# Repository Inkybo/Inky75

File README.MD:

# Inky75 Keyboard

The Inky75 is a custom designed keyboard pcb based on the adafruit KB2040 and using the KMK firmware.

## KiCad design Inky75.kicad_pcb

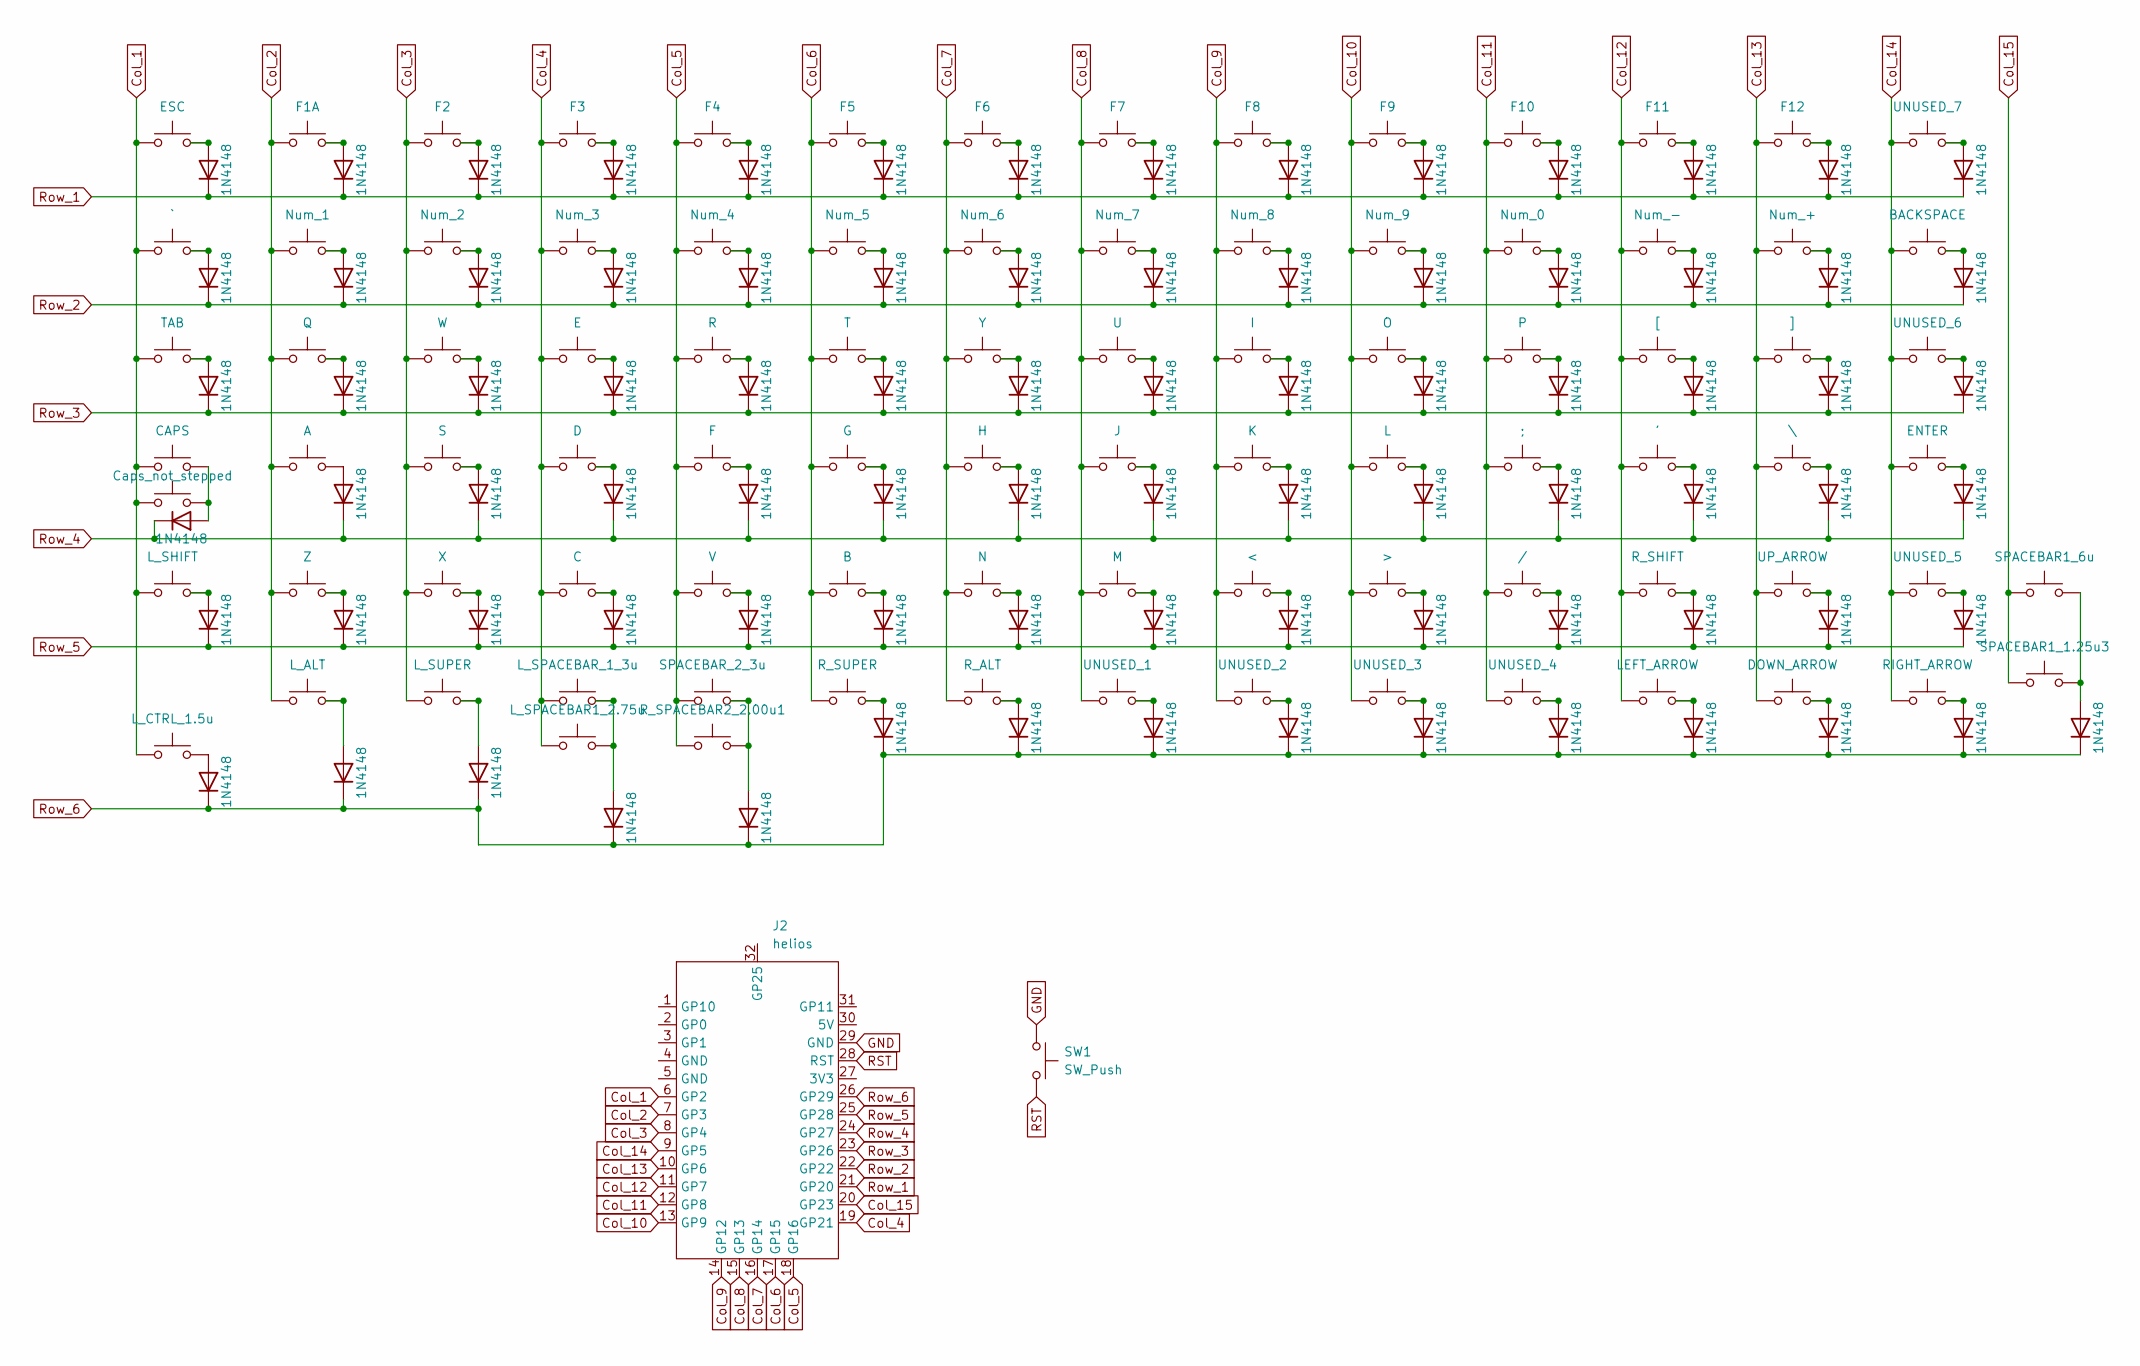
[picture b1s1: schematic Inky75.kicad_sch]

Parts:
'1: '; SW_Cherry_MX_PCB_1.00u
/1: /; SW_Cherry_MX_PCB_1.00u
;1: ;; SW_Cherry_MX_PCB_1.00u
<1: <; SW_Cherry_MX_PCB_1.00u
>1: >; SW_Cherry_MX_PCB_1.00u
A1: A; SW_Cherry_MX_PCB_1.00u
B1: B; SW_Cherry_MX_PCB_1.00u
BACKSPACE1: BACKSPACE; SW_Cherry_MX_PCB_2.00u
C1: C; SW_Cherry_MX_PCB_1.00u
Caps1: CAPS; SW_Cherry_MX_PCB_1.75u
Caps_not_stepped1: Caps_not_stepped; SW_Cherry_MX_PCB_1.25u
D1, D2, D3, D4, D5, D6, D7, D8, D9, D10, D11, D12, D13, D14, D15, D16, D17, D18, D20, D21, D22, D23, D24, D25, D26, D27, D28, D29, D30, D31, D32, D33, D34, D35, D36, D37, D38, D39, D40, D41, D42, D43, D44, D45, D46, D47, D48, D49, D50, D51, D52, D53, D54, D55, D56, D57, D58, D59, D60, D61, D62, D63, D64, D65, D66, D67, D68, D69, D70, D71, D72, D73, D74, D75, D76, D77, D78, D79, D80, D81, D82, D83, D84, D85, D86: 1N4148; D_DO-35_SOD27_P7.62mm_Horizontal
D19: D; SW_Cherry_MX_PCB_1.00u
DOWN_ARROW1: DOWN_ARROW; SW_Cherry_MX_PCB_1.00u
E1: E; SW_Cherry_MX_PCB_1.00u
ENTER1: ENTER; SW_Cherry_MX_PCB_ISOEnter
ESC1: ESC; SW_Cherry_MX_PCB_1.00u
F1: F; SW_Cherry_MX_PCB_1.00u
F1A1: F1A; SW_Cherry_MX_PCB_1.00u
F2: F2; SW_Cherry_MX_PCB_1.00u
F3: F3; SW_Cherry_MX_PCB_1.00u
F4: F4; SW_Cherry_MX_PCB_1.00u
F5: F5; SW_Cherry_MX_PCB_1.00u
F6: F6; SW_Cherry_MX_PCB_1.00u
F7: F7; SW_Cherry_MX_PCB_1.00u
F8: F8; SW_Cherry_MX_PCB_1.00u
F9: F9; SW_Cherry_MX_PCB_1.00u
F10: F10; SW_Cherry_MX_PCB_1.00u
F11: F11; SW_Cherry_MX_PCB_1.00u
F12: F12; SW_Cherry_MX_PCB_1.00u
G1: G; SW_Cherry_MX_PCB_1.00u
H1: H; SW_Cherry_MX_PCB_1.00u
I1: I; SW_Cherry_MX_PCB_1.00u
J1: J; SW_Cherry_MX_PCB_1.00u
J2: helios; helios_no-usb
K1: K; SW_Cherry_MX_PCB_1.00u
L1: L; SW_Cherry_MX_PCB_1.00u
LEFT_ARROW1: LEFT_ARROW; SW_Cherry_MX_PCB_1.00u
L_ALT1: L_ALT; SW_Cherry_MX_PCB_1.25u
L_CTRL_1.5u1: L_CTRL_1.5u; SW_Cherry_MX_PCB_1.50u
L_SHIFT1: L_SHIFT; SW_Cherry_MX_PCB_2.25u
L_SPACEBAR1: L_SPACEBAR_1_3u; SW_Cherry_MX_PCB_3.00u
L_SPACEBAR1_2.75u1: L_SPACEBAR1_2.75u; SW_Cherry_MX_PCB_2.75u
L_SUPER1: L_SUPER; SW_Cherry_MX_PCB_1.50u
M1: M; SW_Cherry_MX_PCB_1.00u
N1: N; SW_Cherry_MX_PCB_1.00u
Num_0: Num_0; SW_Cherry_MX_PCB_1.00u
Num_1: Num_1; SW_Cherry_MX_PCB_1.00u
Num_2: Num_2; SW_Cherry_MX_PCB_1.00u
Num_3: Num_3; SW_Cherry_MX_PCB_1.00u
Num_4: Num_4; SW_Cherry_MX_PCB_1.00u
Num_5: Num_5; SW_Cherry_MX_PCB_1.00u
Num_6: Num_6; SW_Cherry_MX_PCB_1.00u
Num_7: Num_7; SW_Cherry_MX_PCB_1.00u
Num_8: Num_8; SW_Cherry_MX_PCB_1.00u
Num_9: Num_9; SW_Cherry_MX_PCB_1.00u
Num_+1: Num_+; SW_Cherry_MX_PCB_1.00u
Num_-1: Num_-; SW_Cherry_MX_PCB_1.00u
O1: O; SW_Cherry_MX_PCB_1.00u
P1: P; SW_Cherry_MX_PCB_1.00u
Q1: Q; SW_Cherry_MX_PCB_1.00u
R1: R; SW_Cherry_MX_PCB_1.00u
RIGHT_ARROW1: RIGHT_ARROW; SW_Cherry_MX_PCB_1.00u
R_ALT1: R_ALT; SW_Cherry_MX_PCB_1.50u
R_SHIFT1: R_SHIFT; SW_Cherry_MX_PCB_1.75u
R_SPACEBAR2_2.00u1: R_SPACEBAR2_2.00u1; SW_Cherry_MX_PCB_2.00u
R_SUPER1: R_SUPER; SW_Cherry_MX_PCB_1.50u
S1: S; SW_Cherry_MX_PCB_1.00u
SPACEBAR1_1.25u3: SPACEBAR1_1.25u3; SW_Cherry_MX_PCB_1.25u
SPACEBAR1_6u1: SPACEBAR1_6u; SW_Cherry_MX_PCB_6.00u
SPACEBAR_2: SPACEBAR_2_3u; SW_Cherry_MX_PCB_3.00u
SW1: SW_Push; SW_SPST_TL3342
T1: T; SW_Cherry_MX_PCB_1.00u
Tab1: TAB; SW_Cherry_MX_PCB_1.50u
U2: U; SW_Cherry_MX_PCB_1.00u
UNUSED_1: UNUSED_1; SW_Cherry_MX_PCB_1.00u
UNUSED_2: UNUSED_2; SW_Cherry_MX_PCB_1.00u
UNUSED_3: UNUSED_3; SW_Cherry_MX_PCB_1.00u
UNUSED_4: UNUSED_4; SW_Cherry_MX_PCB_1.00u
UNUSED_5: UNUSED_5; SW_Cherry_MX_PCB_1.00u
UNUSED_6: UNUSED_6; SW_Cherry_MX_PCB_1.00u
UNUSED_7: UNUSED_7; SW_Cherry_MX_PCB_1.00u
UP_ARROW1: UP_ARROW; SW_Cherry_MX_PCB_1.00u
V1: V; SW_Cherry_MX_PCB_1.00u
W1: W; SW_Cherry_MX_PCB_1.00u
X1: X; SW_Cherry_MX_PCB_1.00u
Y1: Y; SW_Cherry_MX_PCB_1.00u
Z1: Z; SW_Cherry_MX_PCB_1.00u
[1: [; SW_Cherry_MX_PCB_1.00u
\1: \; SW_Cherry_MX_PCB_1.00u
]1: ]; SW_Cherry_MX_PCB_1.00u
`1: `; SW_Cherry_MX_PCB_1.00u

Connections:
Col_1: Caps1.1, Caps_not_stepped1.1, ESC1.1, J2.6 (GP2), L_CTRL_1.5u1.1, L_SHIFT1.1, Tab1.1, `1.1
Col_2: A1.1, F1A1.1, J2.7 (GP3), L_ALT1.1, Num_1.1, Q1.1, Z1.1
Col_3: F2.1, J2.8 (GP4), L_SUPER1.1, Num_2.1, S1.1, W1.1, X1.1
Col_4: C1.1, D19.1, E1.1, F3.1, J2.19 (GP21), L_SPACEBAR1.1, L_SPACEBAR1_2.75u1.1, Num_3.1
Col_5: F1.1, F4.1, J2.18 (GP16), Num_4.1, R1.1, R_SPACEBAR2_2.00u1.1, SPACEBAR_2.1, V1.1
Col_6: B1.1, F5.1, G1.1, J2.17 (GP15), Num_5.1, R_SUPER1.1, T1.1
Col_7: F6.1, H1.1, J2.16 (GP14), N1.1, Num_6.1, R_ALT1.1, Y1.1
Col_8: F7.1, J1.1, J2.15 (GP13), M1.1, Num_7.1, U2.1, UNUSED_1.1
Col_9: <1.1, F8.1, I1.1, J2.14 (GP12), K1.1, Num_8.1, UNUSED_2.1
Col_10: >1.1, F9.1, J2.13 (GP9), L1.1, Num_9.1, O1.1, UNUSED_3.1
Col_11: /1.1, ;1.1, F10.1, J2.12 (GP8), Num_0.1, P1.1, UNUSED_4.1
Col_12: '1.1, F11.1, J2.11 (GP7), LEFT_ARROW1.1, Num_-1.1, R_SHIFT1.1, [1.1
Col_13: DOWN_ARROW1.1, F12.1, J2.10 (GP6), Num_+1.1, UP_ARROW1.1, \1.1, ]1.1
Col_14: BACKSPACE1.1, ENTER1.1, J2.9 (GP5), RIGHT_ARROW1.1, UNUSED_5.1, UNUSED_6.1, UNUSED_7.1
Col_15: J2.20 (GP23), SPACEBAR1_1.25u3.1, SPACEBAR1_6u1.1
GND: J2.29 (GND), SW1.1
unnamed: '1.2, D71.2 (A)
unnamed: /1.2, D66.2 (A)
unnamed: ;1.2, D65.2 (A)
unnamed: <1.2, D54.2 (A)
unnamed: >1.2, D60.2 (A)
unnamed: A1.2, D10.2 (A)
unnamed: B1.2, D36.2 (A)
unnamed: BACKSPACE1.2, D83.2 (A)
unnamed: C1.2, D24.2 (A)
unnamed: Caps1.2, Caps_not_stepped1.2, D4.2 (A)
unnamed: D1.2 (A), ESC1.2
unnamed: D2.2 (A), `1.2
unnamed: D3.2 (A), Tab1.2
unnamed: D5.2 (A), L_SHIFT1.2
unnamed: D6.2 (A), L_CTRL_1.5u1.2
unnamed: D7.2 (A), F1A1.2
unnamed: D8.2 (A), Num_1.2
unnamed: D9.2 (A), Q1.2
unnamed: D11.2 (A), Z1.2
unnamed: D12.2 (A), L_ALT1.2
unnamed: D13.2 (A), F2.2
unnamed: D14.2 (A), Num_2.2
unnamed: D15.2 (A), W1.2
unnamed: D16.2 (A), S1.2
unnamed: D17.2 (A), X1.2
unnamed: D18.2 (A), L_SUPER1.2
unnamed: D19.2, D23.2 (A)
unnamed: D20.2 (A), F3.2
unnamed: D21.2 (A), Num_3.2
unnamed: D22.2 (A), E1.2
unnamed: D25.2 (A), L_SPACEBAR1.2, L_SPACEBAR1_2.75u1.2
unnamed: D26.2 (A), F4.2
unnamed: D27.2 (A), Num_4.2
unnamed: D28.2 (A), R1.2
unnamed: D29.2 (A), F1.2
unnamed: D30.2 (A), V1.2
unnamed: D31.2 (A), R_SPACEBAR2_2.00u1.2, SPACEBAR_2.2
unnamed: D32.2 (A), F5.2
unnamed: D33.2 (A), Num_5.2
unnamed: D34.2 (A), T1.2
unnamed: D35.2 (A), G1.2
unnamed: D37.2 (A), R_SUPER1.2
unnamed: D38.2 (A), F6.2
unnamed: D39.2 (A), Num_6.2
unnamed: D40.2 (A), Y1.2
unnamed: D41.2 (A), H1.2
unnamed: D42.2 (A), N1.2
unnamed: D43.2 (A), R_ALT1.2
unnamed: D44.2 (A), F7.2
unnamed: D45.2 (A), Num_7.2
unnamed: D46.2 (A), U2.2
unnamed: D47.2 (A), J1.2
unnamed: D48.2 (A), M1.2
unnamed: D49.2 (A), UNUSED_1.2
unnamed: D50.2 (A), F8.2
unnamed: D51.2 (A), Num_8.2
unnamed: D52.2 (A), I1.2
unnamed: D53.2 (A), K1.2
unnamed: D55.2 (A), UNUSED_2.2
unnamed: D56.2 (A), F9.2
unnamed: D57.2 (A), Num_9.2
unnamed: D58.2 (A), O1.2
unnamed: D59.2 (A), L1.2
unnamed: D61.2 (A), UNUSED_4.2
unnamed: D62.2 (A), F10.2
unnamed: D63.2 (A), Num_0.2
unnamed: D64.2 (A), P1.2
unnamed: D67.2 (A), UNUSED_3.2
unnamed: D68.2 (A), F11.2
unnamed: D69.2 (A), Num_-1.2
unnamed: D70.2 (A), [1.2
unnamed: D72.2 (A), R_SHIFT1.2
unnamed: D73.2 (A), LEFT_ARROW1.2
unnamed: D74.2 (A), F12.2
unnamed: D75.2 (A), Num_+1.2
unnamed: D76.2 (A), ]1.2
unnamed: D77.2 (A), \1.2
unnamed: D78.2 (A), UP_ARROW1.2
unnamed: D79.2 (A), DOWN_ARROW1.2
unnamed: D80.2 (A), UNUSED_7.2
unnamed: D81.2 (A), ENTER1.2
unnamed: D82.2 (A), UNUSED_6.2
unnamed: D84.2 (A), UNUSED_5.2
unnamed: D85.2 (A), RIGHT_ARROW1.2
unnamed: D86.2 (A), SPACEBAR1_1.25u3.2, SPACEBAR1_6u1.2
RST: J2.28 (RST), SW1.2
Row_1: D1.1 (K), D7.1 (K), D13.1 (K), D20.1 (K), D26.1 (K), D32.1 (K), D38.1 (K), D44.1 (K), D50.1 (K), D56.1 (K), D62.1 (K), D68.1 (K), D74.1 (K), D80.1 (K), J2.21 (GP20)
Row_2: D2.1 (K), D8.1 (K), D14.1 (K), D21.1 (K), D27.1 (K), D33.1 (K), D39.1 (K), D45.1 (K), D51.1 (K), D57.1 (K), D63.1 (K), D69.1 (K), D75.1 (K), D83.1 (K), J2.22 (GP22)
Row_3: D3.1 (K), D9.1 (K), D15.1 (K), D22.1 (K), D28.1 (K), D34.1 (K), D40.1 (K), D46.1 (K), D52.1 (K), D58.1 (K), D64.1 (K), D70.1 (K), D76.1 (K), D82.1 (K), J2.23 (GP26)
Row_4: D4.1 (K), D10.1 (K), D16.1 (K), D23.1 (K), D29.1 (K), D35.1 (K), D41.1 (K), D47.1 (K), D53.1 (K), D59.1 (K), D65.1 (K), D71.1 (K), D77.1 (K), D81.1 (K), J2.24 (GP27)
Row_5: D5.1 (K), D11.1 (K), D17.1 (K), D24.1 (K), D30.1 (K), D36.1 (K), D42.1 (K), D48.1 (K), D54.1 (K), D60.1 (K), D66.1 (K), D72.1 (K), D78.1 (K), D84.1 (K), J2.25 (GP28)
Row_6: D6.1 (K), D12.1 (K), D18.1 (K), D25.1 (K), D31.1 (K), D37.1 (K), D43.1 (K), D49.1 (K), D55.1 (K), D61.1 (K), D67.1 (K), D73.1 (K), D79.1 (K), D85.1 (K), D86.1 (K), J2.26 (GP29)

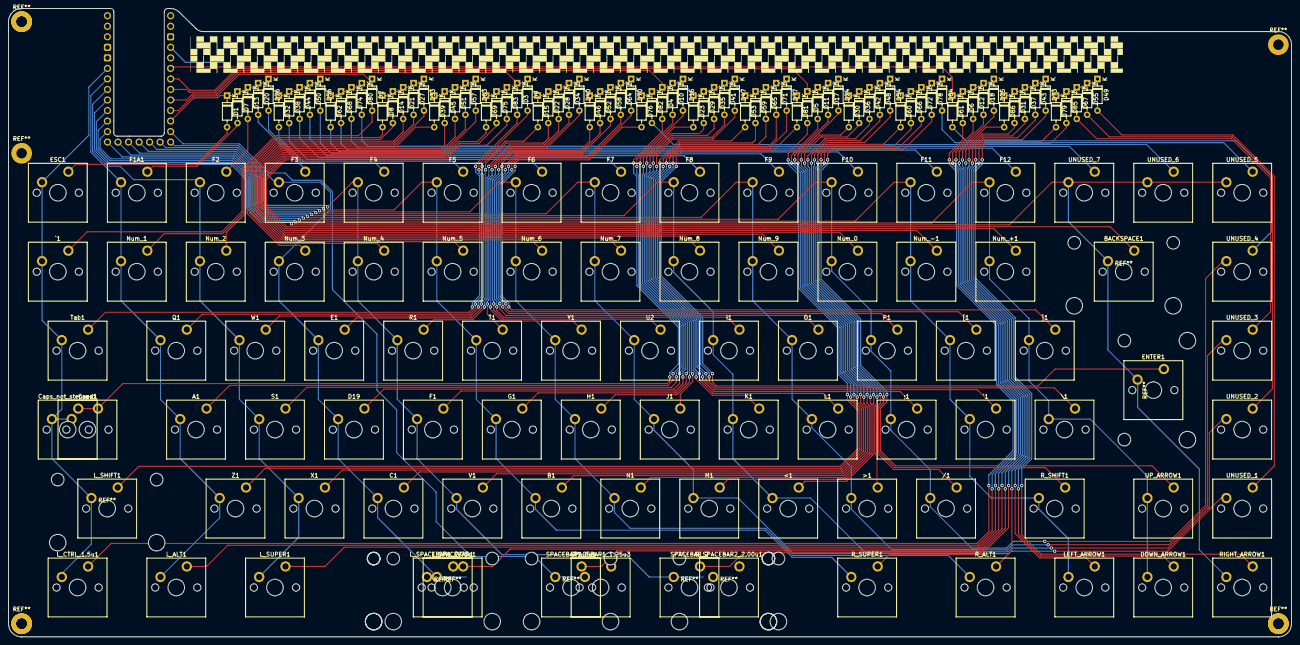
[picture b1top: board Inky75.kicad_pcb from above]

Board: 2 copper layers, 309.5 x 151.6 mm, 177 parts (1 on the bottom side), 108 nets.

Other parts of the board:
Ref**: Val**; barleycorn_logo

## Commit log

2023-01-26 inital commit
2023-01-31 started tidying traces
2023-02-11 fixing traces
2023-02-21 finished routing traces
2023-04-06 updated traces
